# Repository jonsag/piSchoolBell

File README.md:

# piSchoolBell

This runs a Raspberry Pi as a controller for a school bell.  
It makes the school bell ring at the right times taking the calendar into consideration.  
Also there is an LCD screen to visualize time, database stats, upcoming rings etc.  

Administration of the school bell is done via a web UI.  

It is written entirely in python.  

Also it installs gpio-watch to catch the buttons connected to the Pi's GPIO. [https://github.com/larsks/gpio-watch](https://github.com/larsks/gpio-watch)  

## Updates

### 3/7 -22

Now running on RaspberryPiOS Bullseye.  
Everything updated to run on python3.  
Updated install script.  
Made it easier for those not having the Swedish holidays. (More work needed...)  
New module for printing to LCD.  
Fixed apache not defaulting to index.py.  

### 30/6 -22

The API for Swedish holidays, api.dryg.net, is dead.  
Substituted by [sholiday.faboul.se](https://sholiday.faboul.se/dagar/).  

### 7/3 -20

Changed all GPIO pins to make an easier PCB layout possible.  
This makes all older electric installs incompatible.  
Added KiCad files for new pin layout.  

Corrected editing of ring times.  

### 6/3 -20

Bug discovered  
There was a fault in the database setup.  
Instead of updating, you can:  
Log in to database  
>$ sudo mysql -u root -p piSchoolBell  

Change column type  
>MariaDB [piSchoolBell]> ALTER TABLE ringTimes CHANGE weekDays weekDays VARCHAR(7);  

## Hardware setup

### Parts list

* 1 x Raspberry Pi 3 B+, kjell.com Art#88100 (could be any of the later models)  
* 1 x LCD display, kjell.com Art#90215 (16x2 characters, based on the HD44780 chip)  
* 1 x USB micro power adapter, kjell.com Art#88525  
* 1 x Micro SD card, kjell.com Art#97600  
* 1 x 10k potentiometer, kjell.com Art#90633  
* 1 x 5V relay module, kjell.com Art#87878  
* 4 x Push button, kjell.com Art#36023  
* 4 x 10k resistor  
* 4 x 1k resistor  
* 1 x Switch, kjell.com Art#36016  
* 1 x Casing for rpi, kjell.com Art#89030  
* 1 x Casing for relay, kjell.com Art#89014  
* 1 x RTC-module, kjell.com Art#87984  
* 1 x CR2032 battery, kjell.com ART#33715  
* GPIO header connector, kjell.com Art#87915 (or breakout board)  
* Wiring, cables  
* PCB board, kjell.com Art#89416 or Art#89435 (or a breadboard, just to set it up)  

* Soldering material  

### The build  

Assemble all the parts according to the KiCad files.  

### Install and configure OS

Download RaspberryPiOS Lite from [https://www.raspberrypi.com/software/operating-systems/](https://www.raspberrypi.com/software/operating-systems/).  

Cd to where your download is.  
>$ xz -d 2022-04-04-raspios-bullseye-armhf-lite.img.xz  

Insert SD-card and find out drive letter.  
>$ dmesg  

For example '/dev/mmcblk0' or '/dev/sdb'.  

Unmount if mounted.  
>$ umount /dev/mmcblk0p1  
>$ umount /dev/mmcblk0p2  

Write image to SD-card.  
>$ sudo dd bs=4M if=2022-04-04-raspios-bullseye-armhf-lite.img of=/dev/mmcblk0 conv=fsync status=progress  

Remove SD-card and insert it again to make new partitions visible.  

Mount the first partition.  
>$ sudo mount /dev/mmcblk0p1 /mnt/tmp  

Write empty file to boot partition to enable ssh at boot.  
>$ sudo touch /mnt/tmp/ssh  

Unmount.  
>$ sudo umount /mnt/tmp  

Remove SD-card and insert it in a RPi connected to your local network and boot it up.  

### RPi configuration

For this version of the operating system you should have a monitor and keyboard hooked up at the first boot.  

After some restarts you will start to configure your machine:

* Select keyboard layout  
* Create user and set password. For the sake of this installation it's preferred you set 'pi' as username.  

After this you will have a prompt.  
Find out the ip of the RPi

>$ ifconfig

Connect to the RPi via ssh on another machine (if you don't want to continue as before).  

>$ ssh -ip from above-  -l pi  

Login with the username and password you created earlier  

### Configure

>$ sudo raspi-config  

1 S1    Configure wifi  
2 S4    Change hostname  
4 P2    Set GPU memory to 16  
5 L1    Set locales  
5 L2    Set time zone  
6 A1    Expand file system to use whole SD-card  

Reboot to set new options.  

### Update OS

Connect again  

>$ sudo apt-get update && sudo apt-get upgrade  

## Installation

### Install git

>$ sudo apt-get install git  

### Clone repository

>$ cd /home/pi  
>$ git clone <https://github.com/jonsag/piSchoolBell.git>  

### Run install script

>$ cd /home/pi/piSchoolBell  
>$ sudo ./install.sh  

### Initialize mysql (mariadb)

>$ sudo mysql_secure_installation  

Set root password, and press 'enter' on all other questions

### Create database

>$ sudo /home/pi/piSchoolBell/mysql-setup.sh  

### Add test data, if wanted (otherwise some things will act funny until you create your own entries)  

>$ /home/pi/piSchoolBell/insertTestData.sh  

### Download (Swedish) dates

>$ /home/pi/bin/piSchoolBell/getCalendar.py -v  

### For those living outside of Sweden

If you're not lucky enough to live in Sweden, you can run this to make all weekdays workdays.  

>$ /home/pi/piSchoolBell/makeAllWeekdaysToWorkdays.sh

This includes ALL Mondays to Fridays.  

You will have to manually add your own work free weekdays.  

To set 4'th of July 2023 to work free day (if it wasn't a Sunday already...)  
Connect to mysql  

>$ mysql -u pi -p$(grep password /home/pi/bin/piSchoolBell/mysql-config.ini | awk '{ print $3 }') piSchoolBell
>
>MariaDB [piSchoolBell]> UPDATE days SET isWorkDay = '0' WHERE date = '2023-06-04';

#### Note

In Sweden we use the correct way for dates and numbering days.  

The first day of the week is Monday. It has number '0' in the database.  
When printing dates we use 'YYYY-MM-DD'.  

### Make web pages secure

>$ sudo /home/pi/piSchoolBell/www-secure-setup.sh  

## If you're adding an RTC module

### Enable i2c

>$ sudo raspi-config  

3 I5    Enable I2C interface  

>$ ./install-rtc.sh  

### Set hardware clock

Check that time and date is correct  

>$ date  

Set hardware clock  

>$ sudo hwclock -w  

Comment out the following lines in /lib/udev/hwclock-set  

    if [ -e /run/systemd/system ] ; then  
        exit 0  
    fi  

Reboot  

## Configuration

Press button on unit to display its IP-address on the second line of the LCD.  
Connect to the unit by pointing your browser to  

    http://\<IP-address\>:8080'.  

Edit or add breaks, ring times and ring patterns.  

Remember, you can't really add rings on saturdays or sundays, as this is mainly intended for use on normal school schedules.  

### Automatic tasks

At the first of every month cron will download calendar from 'dryg.net', adding data to the database.  
Every night cron will delete past breaks and days from the database.  

## Usage

Normally the LCD display shows:  
Line 1: HH:MM YYYY-mm-dd, current time and date  
Line 2: HH:MM YYYY-mm-dd, the time and date for the next bell ring  

By pressing button 1, display will show:  
&nbsp;&nbsp;&nbsp;&nbsp;Line 1: days left in db, last date in db  
&nbsp;&nbsp;&nbsp;&nbsp;Line 2: IP-address  
&nbsp;&nbsp;&nbsp;&nbsp;&nbsp;&nbsp;&nbsp;&nbsp;If it shows 'Not connected' it has not been able to acquire an IP address.  
&nbsp;&nbsp;&nbsp;&nbsp;&nbsp;&nbsp;&nbsp;&nbsp;The first character on line 2 shows if the unit can access internet.  
&nbsp;&nbsp;&nbsp;&nbsp;&nbsp;&nbsp;&nbsp;&nbsp;If it is a '*' it is connected.  
&nbsp;&nbsp;&nbsp;&nbsp;&nbsp;&nbsp;&nbsp;&nbsp;If it is a '-' it is not connected.  

Pressing button 2 will make the LCD go back to showing default info.  

## USE THE BELOW WITH CAUTION, NOT TESTED ENOUGH

To dump database and logs to USB-stick:  
Format a stick to fat32 and label it 'PISCHOOLBEL'.  
Insert into Pi.  
&nbsp;&nbsp;&nbsp;&nbsp;Display will show:  
&nbsp;&nbsp;&nbsp;&nbsp;&nbsp;&nbsp;&nbsp;&nbsp;The USBs label and drive letter  
&nbsp;&nbsp;&nbsp;&nbsp;&nbsp;&nbsp;&nbsp;&nbsp;'USB mounted'  
Press button 3.  
&nbsp;&nbsp;&nbsp;&nbsp;Display will confirm writing  
&nbsp;&nbsp;&nbsp;&nbsp;When finished display shows number of files written  

Remove USB  
&nbsp;&nbsp;&nbsp;&nbsp;Display will show:  
&nbsp;&nbsp;&nbsp;&nbsp;&nbsp;&nbsp;&nbsp;&nbsp;drive letter  
&nbsp;&nbsp;&nbsp;&nbsp;&nbsp;&nbsp;&nbsp;&nbsp;'USB umounted'  

Edit the database file with the highest date and time on the stick.  
To read back edited file to database:  
Insert the USB-stick.  
&nbsp;&nbsp;&nbsp;&nbsp;Display will show:  
&nbsp;&nbsp;&nbsp;&nbsp;&nbsp;&nbsp;&nbsp;&nbsp;The USBs label and drive letter  
&nbsp;&nbsp;&nbsp;&nbsp;&nbsp;&nbsp;&nbsp;&nbsp;'USB mounted'  
Press button 4.  
&nbsp;&nbsp;&nbsp;&nbsp;Display will confirm reading  
&nbsp;&nbsp;&nbsp;&nbsp;...  
Not implemented yet.  
For now it only shows how many lines to read back to the database.  

## Issues

If you get problems with Adafruit_Python_CharLCD failing to write to LCD.  

>$ cd /home/pi/piSchoolBell/Adafruit_Python_CharLCD  
>$ sudo python setup.py install  

## Hardware clock / RTC, quick reference

Check system time:  

>$ date  

Check HW-time:  

>$ sudo hwclock -r  

Set HW-clock to system time:  

>$ sudo hwclock -w  

Set system clock from HW-clock:  

>$ sudo hwclock -s  

Set system date manually:  

>$ date +%Y%m%d -s "20120418"  

Set system time manually:  

>$ date +%T -s "11:14:00"  

Set HW-clock manually:  

>$ sudo hwclock --set --date="2011-08-14 16:45:05"  

## Below is only for my own convenience during programming of this project

>$ rsync -raci ~/Documents/EclipseWorkspace/piSchoolBell/* pi@192.168.10.44:/home/pi/bin/piSchoolBell/  
>$ rsync -raci ~/Documents/EclipseWorkspace/piSchoolBell/www/* pi@192.168.10.44:/var/www/piSchoolBell/  
>$ ssh pi@192.168.10.44 'sudo chmod 755 -R /var/www/piSchoolBell'  
>$ ssh pi@192.168.10.44 'sudo chown -R pi:www-data /var/www/piSchoolBell'  
>$ rsync -raci ~/Documents/EclipseWorkspace/piSchoolBell/purgeDatabase.py pi@192.168.10.44:/home/pi/bin/piSchoolBell/  
>
>$ rsync -raci ~/Documents/CodeWorkspace/piSchoolBell pi@192.168.10.99:/home/pi/  
>$ rsync -raci ~/Documents/CodeWorkspace/piSchoolBell/bin/* pi@192.168.10.99:/home/pi/bin/piSchoolBell  

### Things to check after install

>$ list /home/pi/bin/piSchoolBell/  
>$ cat /home/pi/bin/piSchoolBell/gpio.service  
>$ cat /lib/systemd/system/gpio.service  
>$ list /home/pi/bin/piSchoolBell/gpio-scripts  
>$ cat /home/pi/bin/piSchoolBell/gpio-scripts/gpio-script  
>$ list /var/www/piSchoolBell  
>$ cat etc/cron.d/piSchoolBell  
>$ ps ax | grep gpio  

### Run some tests

>$ /home/pi/bin/piSchoolBell/printToLcd.py -v  
>$ i2cdetect -y 1  
>$ cat /proc/driver/rtc

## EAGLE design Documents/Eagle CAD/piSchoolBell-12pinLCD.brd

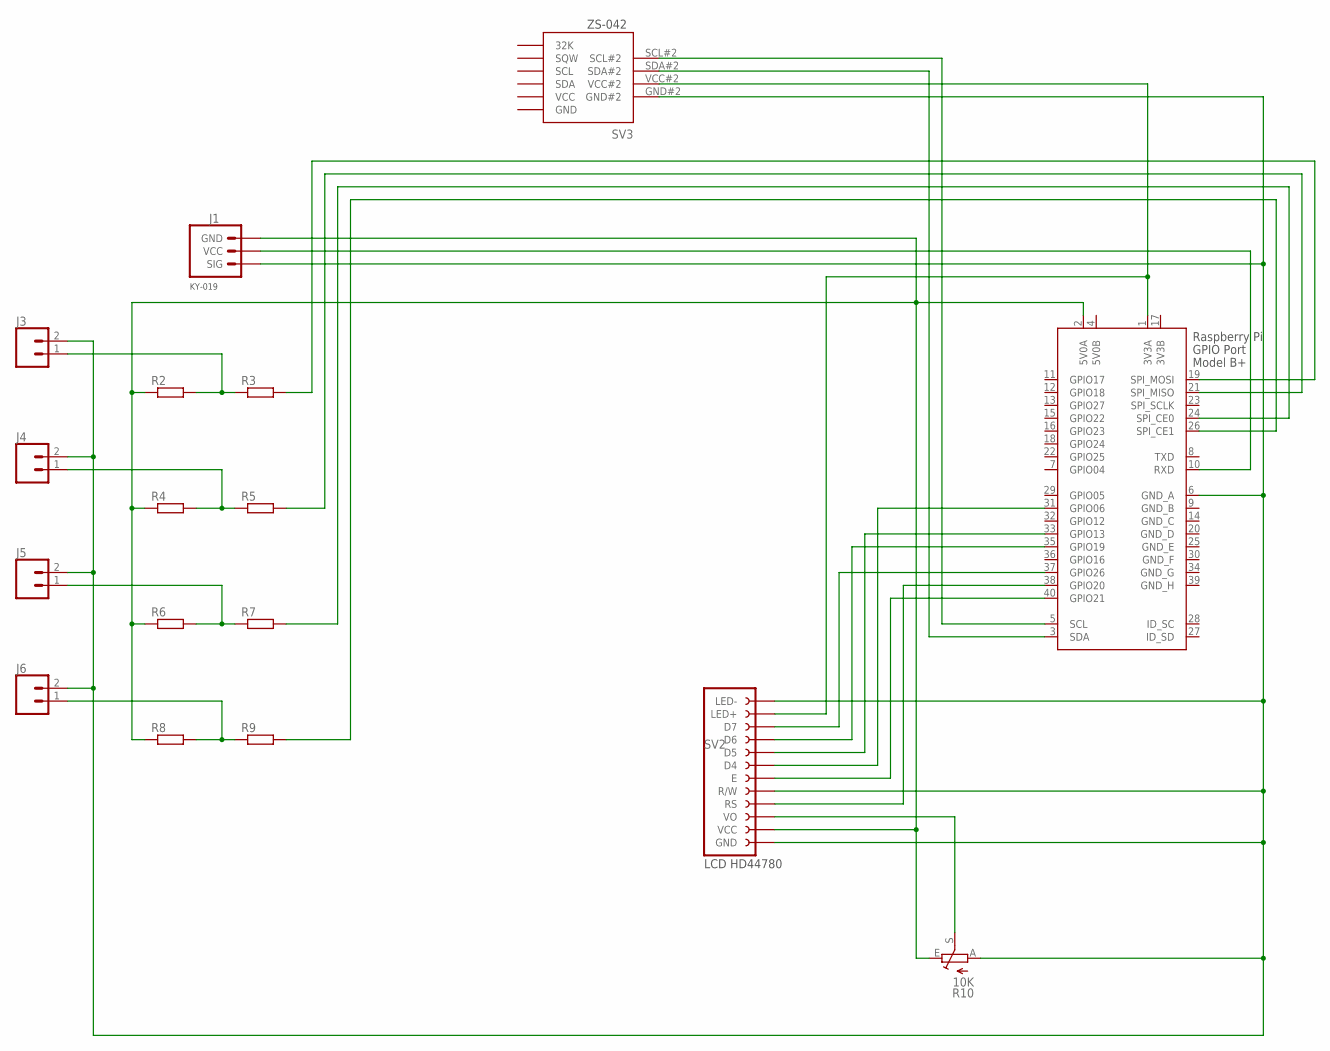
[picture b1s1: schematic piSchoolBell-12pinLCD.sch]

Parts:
J1: 455-1750-1-ND; KY-019_3-PIN_MALE_HEADER
J3, J4, J5, J6: CONN_02; 1X02
R2, R3, R4, R5, R6, R7, R8, R9: R-EU_0204/7; 0204/7
R10: 10K; B25P
SV2: LCD-HD44780-12-PIN_FEMALE_HEADER
SV3: ZS-042_RTC_6+4-PIN_FEMALE_HEADER; ZS-042_RTC_6+4-PIN_FEMALE_HEADER_W_MOUNT_HOLES
X1: RASPI_BOARD_B+#_H; RASPI_BOARD_B+HAT

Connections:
3V3B: X1.17 (3V3B)
5V0B: X1.4 (5V0B)
GND: J1.SIG, J3.2, J4.2, J5.2, J6.2, R10.A, SV2.GND, SV2.LED-, SV2.R/W, SV3.GND#2, X1.6 (GND_A)
GND_B: X1.9 (GND_B)
GND_C: X1.14 (GND_C)
GND_D: X1.20 (GND_D)
GND_E: X1.25 (GND_E)
GND_F: X1.30 (GND_F)
GND_G: X1.34 (GND_G)
GND_H: X1.39 (GND_H)
unnamed: R10.S, SV2.VO
unnamed: SV3.SDA#2, X1.3 (SDA)
unnamed: SV3.SCL#2, X1.5 (SCL)
unnamed: J3.1, R2.2, R3.1
unnamed: R3.2, X1.19 (SPI_MOSI)
unnamed: SV2.RS, X1.38 (GPIO20)
unnamed: SV2.E, X1.40 (GPIO21)
unnamed: SV2.D4, X1.31 (GPIO06)
unnamed: SV2.D5, X1.33 (GPIO13)
unnamed: SV2.D6, X1.35 (GPIO19)
unnamed: J1.GND, R2.1, R4.1, R6.1, R8.1, R10.E, SV2.VCC, X1.2 (5V0A)
unnamed: SV2.D7, X1.37 (GPIO26)
unnamed: SV2.LED+, SV3.VCC#2, X1.1 (3V3A)
unnamed: J4.1, R4.2, R5.1
unnamed: J5.1, R6.2, R7.1
unnamed: J6.1, R8.2, R9.1
unnamed: R5.2, X1.21 (SPI_MISO)
unnamed: R7.2, X1.24 (SPI_CE0)
unnamed: R9.2, X1.26 (SPI_CE1)
unnamed: J1.VCC, X1.10 (RXD)

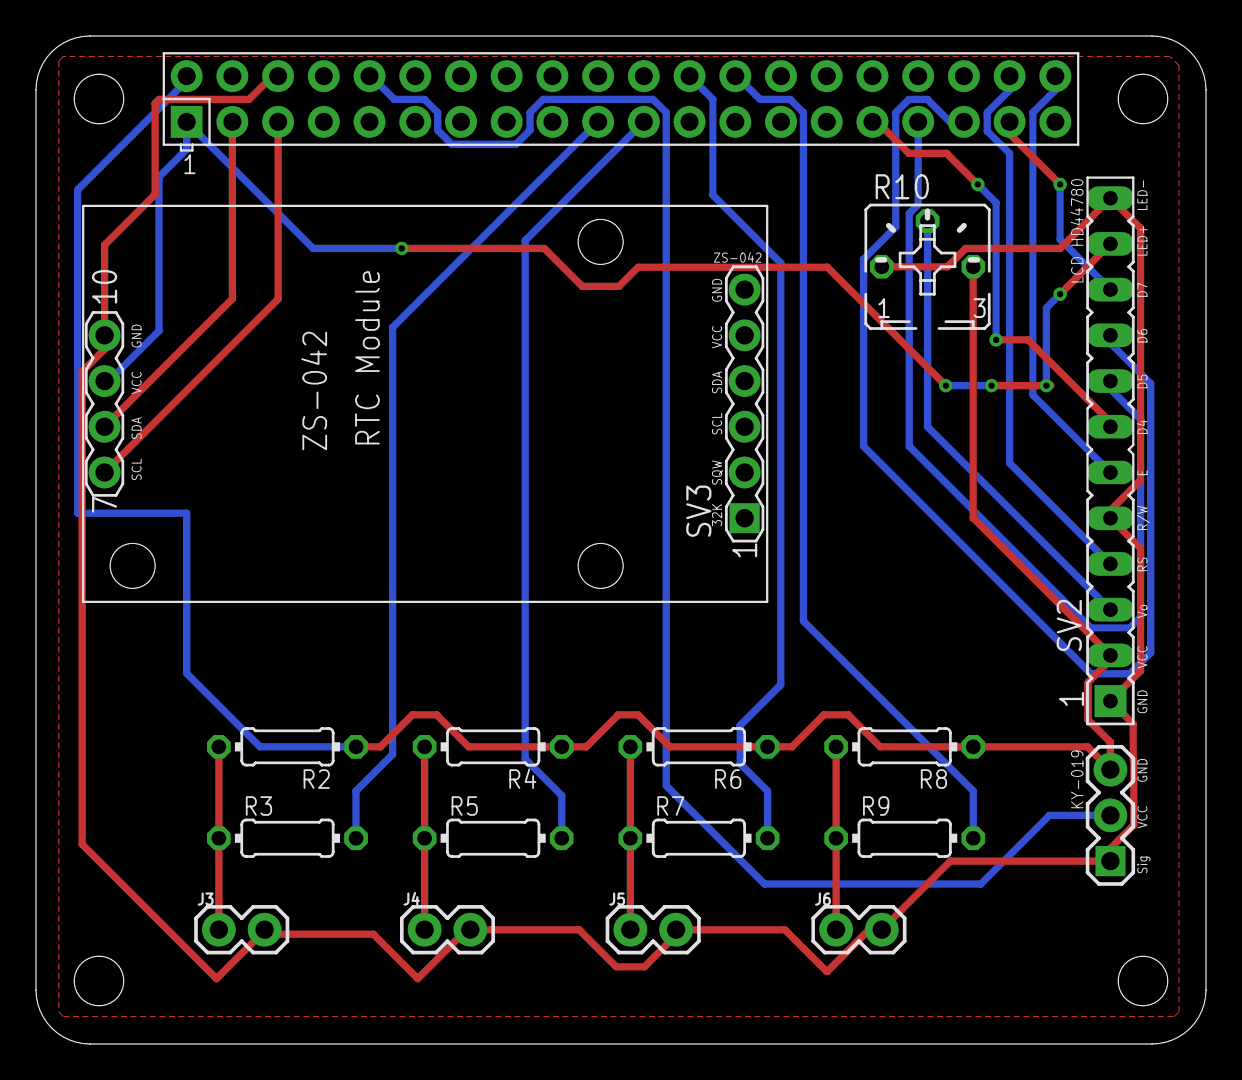
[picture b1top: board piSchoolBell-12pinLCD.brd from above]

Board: 2 copper layers, 65.0 x 56.0 mm, 17 parts (0 on the bottom side), 21 nets.

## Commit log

2018-03-05 Added first python code
2018-03-05 Starting to get calendar events from dryg.net
2018-03-05 Added a start to mysql setup
2018-03-06 Now gets and inserts school days i db
2018-03-07 Now rings bell at correct times and dates
2018-03-08 Now we have apache with in the game
2018-03-09 Now takes extra school days in concern
2018-03-09 Added test data
2018-03-09 Now edits ring patterns
2018-03-10 Now check ring patterns for illegal new entries
2018-03-11 Now we can view and add ring times
2018-03-11 Forgot...
2018-03-11 Now stops used ring patterns from being deleted
2018-03-11 Now we can edit school breaks
2018-03-11 Now displays upcoming ringtimes
2018-03-11 Changed some output on times
2018-03-11 Visual changes
2018-03-12 Prints IP to LCD when pressing button
2018-03-13 GPIO working. Deleted day_name. Created install script.
2018-03-13 Updated install
2018-03-13 Debugging
2018-03-13 My mistake
2018-03-13 New test data. Updated install
2018-03-13 Started on a purge to clean database
2018-03-14 Many updates. Almost done
2018-03-14 Changed web layouts
2018-03-14 More info on status
2018-03-15 Perhaps this would be v1.0b...
2018-03-15 Added file
2018-03-15 Fixed IP detection
2018-03-16 Moved files
2018-03-16 New readme and functions
2018-03-16 Added Documents
2018-03-17 Changed mysql setup
2018-03-17 Started to work on another way to edit the database
2018-03-18 Added scripts for auto mounting USB. Added uninstall.
2018-03-18 Changed permissions on automount
2018-03-18 Moved stuff around
2018-03-19 Now prints to LCD on USB insertion/removal
2018-04-17 Added two more buttons
2018-04-17 Added internet check
2018-04-18 Renamed file. Added dump/read USB
2018-04-18 Updated gpio files
2018-04-18 New install script
2018-04-18 Added RTV install
2018-04-18 Changed format on install
2018-04-18 Converted to dos
2018-04-18 Install dies on any error
2018-04-18 New install
2018-04-18 Finally managed to get RTC working?...
2018-04-18 Added and deleted files. Updated fritzing
2018-04-18 Changed permissions
2018-04-18 Updated fritz
2018-04-19 Many updates
2018-04-25 Added ringbell cron
2018-04-25 Reverted
2018-04-25 Added cron to ring bell
2019-12-21 Added Eagle schematics
2019-12-21 Routed PCB
2019-12-21 Coppper pour on pdfs
2019-12-22 Changed AuthName
2020-03-02 restored file that was deleted by mistake
2020-03-02 realized after viewing install.sh that it was supposed to be deleted...
2020-03-06 fixes bug in database setup
2020-03-06 escaped $ in install to put logs on right place
2020-03-07 fixed updating of ring times concerning ringpattern and weekdays
2020-03-07 new GPIO pins, eagle cad no longer relevant
2020-03-07 all new pin layout, check README!
2020-03-08 kicad
2020-03-08 moved pin for backlight in KiCad
2021-01-30 formatting
2021-04-21 formatted code
2021-11-04 some problem with formatting on last commit
2021-11-04 modules.py is back. Formats
2021-11-04 rm .gitignore
2022-05-17 kicad6
2022-06-12 minor schematic change
2022-06-30 api address changed
2022-07-01 python3 shebang
2022-07-01 formatting code, deleted deprecated library
2022-07-01 deleted Eagle and Fritzing
2022-07-01 lost a citation in uninstall
2022-07-02 sterted work on RPiOS
2022-07-03 seems to work now
2022-07-03 README
2022-07-03 htaccess
2022-07-04 run install.sh extra

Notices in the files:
parts and their libraries:
SparkFun-Connectors: Licensing: Creative Commons ShareAlike 4.0 International - https://creativecommons.org/licenses/by-sa/4.0
